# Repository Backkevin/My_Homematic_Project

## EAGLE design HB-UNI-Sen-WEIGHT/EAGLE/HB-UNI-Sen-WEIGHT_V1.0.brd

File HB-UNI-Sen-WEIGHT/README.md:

# HB-UNI-Sen-WEIGHT

+ HB-UNI-Sen-WEIGHT
	+ V1.0
		* Work 50%
		* 230VAC Version
		* Partlist not OK
	+ Work in progress !
>

### Partslist 230VAC Version
                    
  Part Name   |      PIC      |   Part Info   | Part Quantity |   Part Link 
------------- | ------------- | ------------- | ------------- | -------------
Arduino||Arduino Pro Mini 8Mhz 3.3V|1|[Links](https://de.aliexpress.com/item/32863952987.html?spm=a2g0s.9042311.0.0.27424c4d2YDzey)
CC1101||CC1101 Funkmodul|1|[Links](https://de.aliexpress.com/item/32924239954.html?spm=a2g0s.9042311.0.0.27424c4dO9ofu2)
Config,S1 - S4||Taster 6x6|5|[Links](https://de.aliexpress.com/item/32912263133.html?spm=a2g0s.9042311.0.0.2cb44c4dtuowdv)
LED1 - LED5||LED 3mm|5|[Links](https://de.aliexpress.com/item/32844298998.html?spm=a2g0s.9042311.0.0.27424c4dBW9kvr)
HLK-5M05||HLK-PM01|1|[Links](https://de.aliexpress.com/item/32705471039.html?spm=a2g0s.9042311.0.0.2cb44c4dtuowdv)
F1,F2||Sicherungshalter|2|[Links](https://de.aliexpress.com/item/32817849786.html?spm=a2g0o.productlist.0.0.260073beDSkClD&algo_pvid=51b52a6f-dc94-4152-9721-98bffea40076&algo_expid=51b52a6f-dc94-4152-9721-98bffea40076-1&btsid=c94e558f-368d-470b-a49c-61c69230d3d9&ws_ab_test=searchweb0_0,searchweb201602_2,searchweb201603_52)
R1 - R5||470 Ohm Widerstand|5|[Links](https://de.aliexpress.com/item/32475181535.html?spm=a2g0o.productlist.0.0.d4fa8034p2AKck&s=p&algo_pvid=4976c9e3-6165-4df4-b127-6d9845fdbe12&algo_expid=4976c9e3-6165-4df4-b127-6d9845fdbe12-1&btsid=7a52ff49-9ff4-47d2-965f-007ad481e8b7&ws_ab_test=searchweb0_0,searchweb201602_2,searchweb201603_52)
230V,S1 - S4||Wannenstecker für AKL 249, 2-pol, RM5,08|5|[Links](https://www.reichelt.de/wannenstecker-fuer-akl-249-2-pol-rm5-08-akl-230-02-p36701.html?)
RL1 - RL4||Wannenstecker für AKL 249, 3-pol, RM5,08|4|[Links](https://www.reichelt.de/wannenstecker-fuer-akl-249-3-pol-rm5-08-akl-230-03-p36702.html?)
Arduino||Pin Header Streifen 12 Pin|2|[Links](https://de.aliexpress.com/item/32904918519.html?spm=a2g0s.9042311.0.0.27424c4dCsKCBi)
CC1101||Stiftleiste 20 polig, vergoldet, Raster 2,00mm|1|[Links](https://secure.reichelt.com/lu/de/stiftleiste-20-pol-vergoldet-bkl-10120400-p235635.html?)
C1||50V10UF|1|[Links](https://de.aliexpress.com/item/32741687066.html?spm=a2g0o.productlist.0.0.4d225216N68Cr1&algo_pvid=dbcb75f4-e623-4355-8aa4-ccd3a7b65d32&algo_expid=dbcb75f4-e623-4355-8aa4-ccd3a7b65d32-3&btsid=a9b8176e-1372-45d7-a781-8d3fc9fab8e5&ws_ab_test=searchweb0_0,searchweb201602_2,searchweb201603_52)
Sabotage,Arduino||Jumper|1|[Links](https://de.aliexpress.com/item/32873263301.html?spm=a2g0o.productlist.0.0.18ea263dluRsmQ&algo_pvid=b495ebad-e4de-4809-a086-8143c1f9f12b&algo_expid=b495ebad-e4de-4809-a086-8143c1f9f12b-2&btsid=53bb7c29-6fd7-4471-b8c4-bc2766b36d10&ws_ab_test=searchweb0_0,searchweb201602_2,searchweb201603_52)
Modul||Last Zelle Widerstand|1|[Links](https://de.aliexpress.com/item/33049336194.html?spm=a2g0s.9042311.0.0.27424c4durraPx)
-|-|-|-
OPTIONAL||FT232RL USB zu TTL Serielle Adapter|1|[Links](https://de.aliexpress.com/item/32846166237.html?spm=a2g0s.9042311.0.0.27424c4dQGznlY)

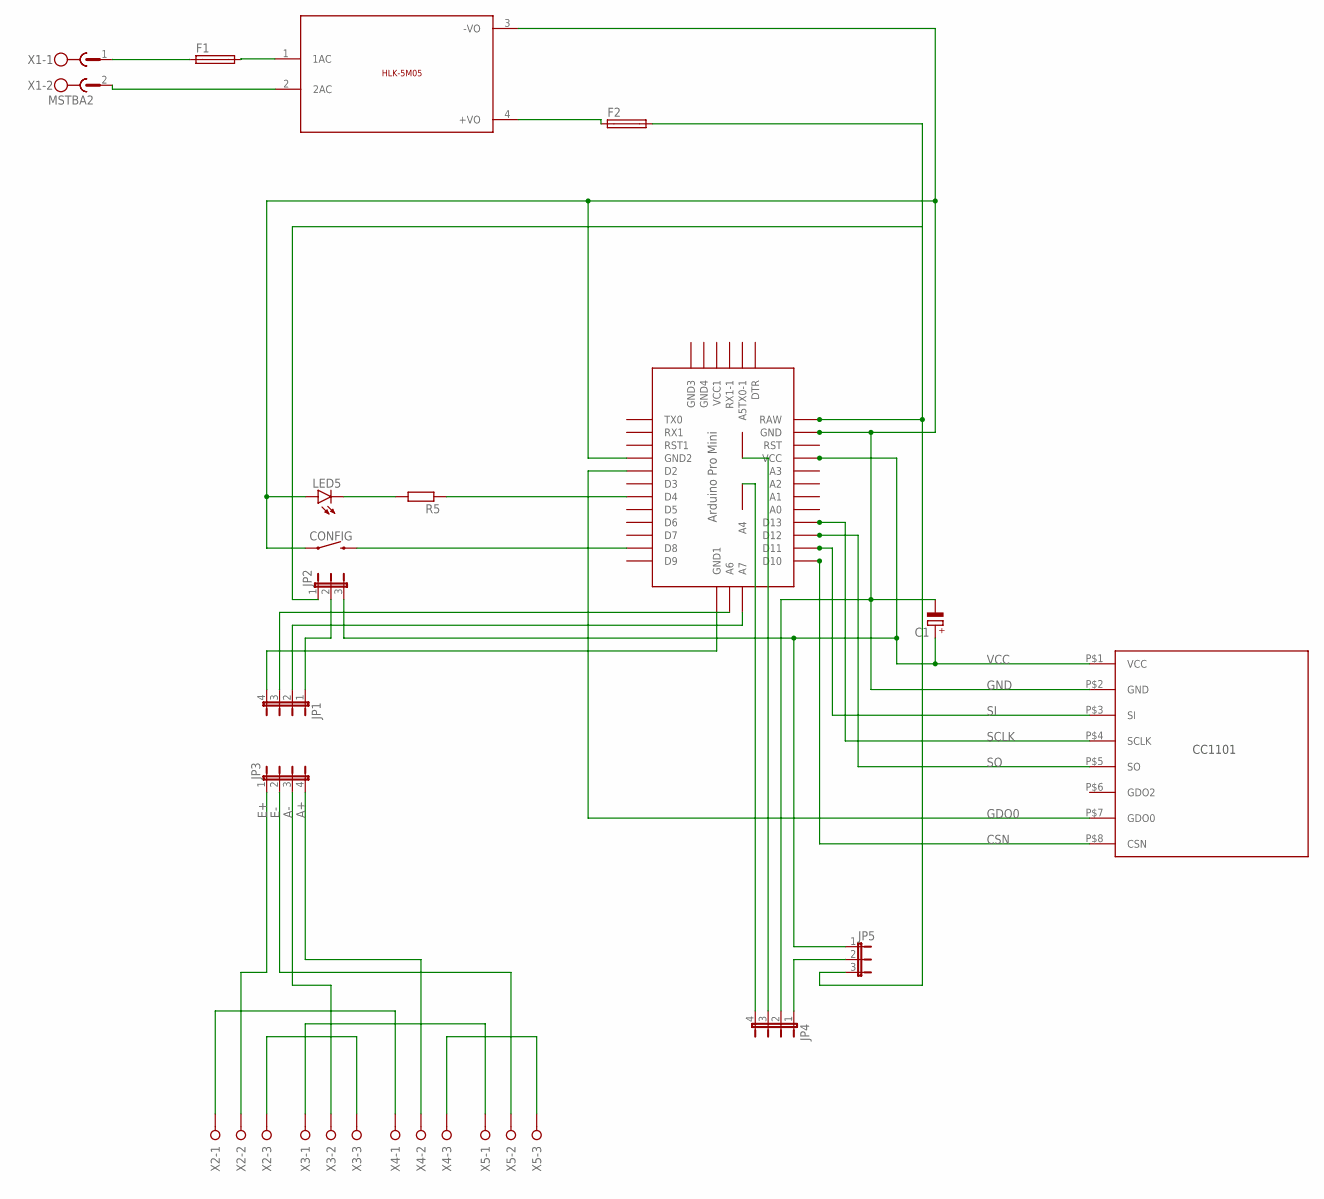
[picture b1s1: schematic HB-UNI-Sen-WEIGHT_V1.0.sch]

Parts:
C1: CPOL-EUE2.5-5; E2,5-5
CONFIG: MOMENTARY-SWITCH-SPST-PTH-6.0MM-KIT; TACTILE_SWITCH_PTH_6.0MM_KIT
F1, F2: SH22,5A
JP1, JP3, JP4: JP4E; JP4
JP2, JP5: JP2E; JP2
LED5: LED3MM
R5: R-EU_0309/10; 0309/10
U$1: CC1101
U$2: ABK-PRO-MINI
U$3: 5VDC/5W; HLK-5M05
X1: MSTBA2
X2, X3, X4, X5: W237-03P; W237-133

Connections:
A+: JP3.4, X4.2
A-: JP3.3, X3.2
CSN: U$1.P$8 (CSN), U$2.D10
E+: JP3.1, X2.2
E-: JP3.2, X5.2
GDO0: U$1.P$7 (GDO0), U$2.D2
GND: C1.-, CONFIG.1, JP4.2, LED5.A, U$1.P$2 (GND), U$2.GND, U$2.GND1 (GND2), U$3.3 (-VO)
unnamed: JP1.1, JP2.2
unnamed: JP1.3, U$2.A6
unnamed: JP1.2, U$2.A7
unnamed: JP1.4, U$2.GND4 (GND1)
unnamed: JP4.1, JP5.2
unnamed: JP4.4, U$2.A4
unnamed: JP4.3, U$2.A5
unnamed: X2.1, X4.1
unnamed: F1.1, X1.1
unnamed: F2.1, U$3.4 (+VO)
unnamed: U$3.2 (2AC), X1.2
unnamed: X3.1, X5.1
unnamed: X2.3, X3.3
unnamed: X4.3, X5.3
unnamed: CONFIG.3 (2), U$2.D8
unnamed: R5.1, U$2.D4
unnamed: LED5.K (C), R5.2
unnamed: F1.2, U$3.1 (1AC)
unnamed: F2.2, JP2.1, JP5.3, U$2.RAW
SCLK: U$1.P$4 (SCLK), U$2.D13
SI: U$1.P$3 (SI), U$2.D11
SO: U$1.P$5 (SO), U$2.D12
VCC: C1.+, JP2.3, JP5.1, U$1.P$1 (VCC), U$2.VCC

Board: 2 copper layers, 19 parts (0 on the bottom side), 30 nets, no tracks yet.

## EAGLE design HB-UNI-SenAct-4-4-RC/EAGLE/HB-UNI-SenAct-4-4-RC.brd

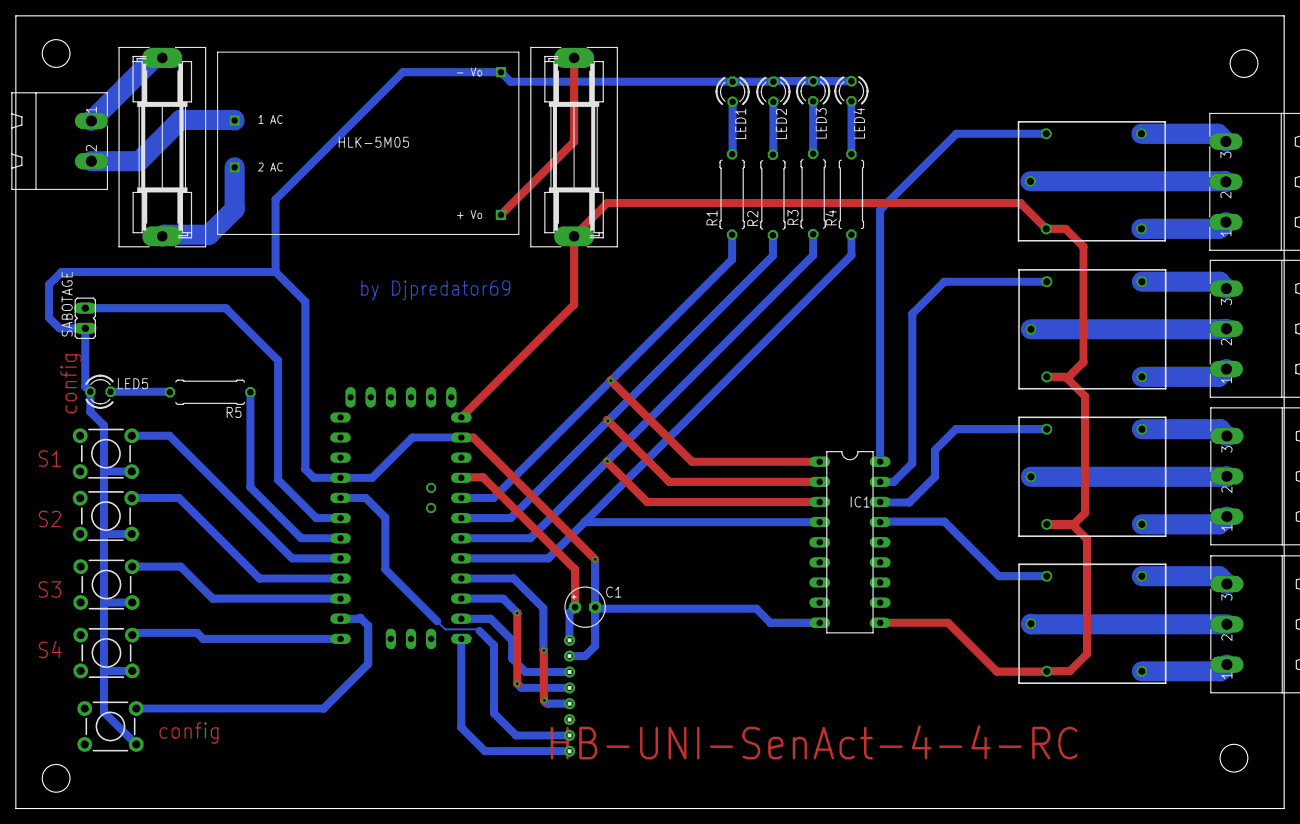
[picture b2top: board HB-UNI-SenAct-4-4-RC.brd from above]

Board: 2 copper layers, 160.0 x 100.0 mm, 32 parts (0 on the bottom side), 44 nets.

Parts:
C1: E2,5-5
CONFIG: MOMENTARY-SWITCH-SPST-PTH-6.0MM-KIT; TACTILE_SWITCH_PTH_6.0MM_KIT
F1, F2: SH22,5A
IC1: DIL18
LED1, LED2, LED3, LED4, LED5: LED3MM
R1, R2, R3, R4, R5: 0309/10
S1, S2, S3, S4: MOMENTARY-SWITCH-SPST-PTH-6.0MM-KIT; TACTILE_SWITCH_PTH_6.0MM_KIT
SABOTAGE: JP1
U$1: 1X8
U$2: ABK-PRO-MINI
U$3: 5VDC/5W; HLK-5M05
U$4, U$5, U$6, U$7: RELAYPTH; SRD-05VDC-SL-C
X1: MSTBA2
X2, X3, X4, X5: MSTBA3

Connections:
CSN: U$1.8, U$2.D10
GDO0: U$1.7, U$2.D2
GND: C1.-, CONFIG.1, IC1.9, LED1.A, LED2.A, LED3.A, LED4.A, LED5.A, S1.1, S2.1, S3.1, S4.1, SABOTAGE.1, U$1.2, U$2.GND, U$2.GND1, U$3.3
unnamed: IC1.1, R1.1, U$2.A0
unnamed: IC1.2, R2.1, U$2.A1
unnamed: IC1.3, R3.1, U$2.A2
unnamed: IC1.4, R4.1, U$2.A3
unnamed: LED1.K, R1.2
unnamed: LED2.K, R2.2
unnamed: LED3.K, R3.2
unnamed: LED4.K, R4.2
unnamed: F1.1, X1.1
unnamed: F2.1, U$3.4
unnamed: U$3.2, X1.2
unnamed: S1.3, U$2.D5
unnamed: S2.3, U$2.D6
unnamed: S3.3, U$2.D7
unnamed: S4.3, U$2.D9
unnamed: CONFIG.3, U$2.D8
unnamed: R5.1, U$2.D4
unnamed: LED5.K, R5.2
unnamed: F1.2, U$3.1
unnamed: SABOTAGE.2, U$2.D3
unnamed: U$6.SWCLOSED, X4.1
unnamed: U$7.SWCOMMON, X5.2
unnamed: U$6.SWOPEN, X4.3
unnamed: F2.2, IC1.10, U$2.RAW, U$4.COIL0, U$5.COIL0, U$6.COIL0, U$7.COIL0
unnamed: U$7.SWCLOSED, X5.1
unnamed: U$6.SWCOMMON, X4.2
unnamed: U$7.SWOPEN, X5.3
unnamed: U$5.SWOPEN, X3.3
unnamed: U$5.SWCOMMON, X3.2
unnamed: U$5.SWCLOSED, X3.1
unnamed: U$4.SWOPEN, X2.3
unnamed: U$4.SWCOMMON, X2.2
unnamed: U$4.SWCLOSED, X2.1
unnamed: IC1.18, U$4.COIL1
unnamed: IC1.17, U$5.COIL1
unnamed: IC1.16, U$6.COIL1
unnamed: IC1.15, U$7.COIL1
SCLK: U$1.4, U$2.D12
SI: U$1.3, U$2.D11
SO: U$1.5, U$2.D13
VCC: C1.+, U$1.1, U$2.VCC

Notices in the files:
parts and their libraries:
SparkFun-Switches: Licensing: Creative Commons ShareAlike 4.0 International - https://creativecommons.org/licenses/by-sa/4.0
